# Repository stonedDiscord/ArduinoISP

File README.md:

# ArduinoISP

A PCB to use an Arduino Nano as an In-Circuit Serial Programmer (ISP) for programming AVR microcontrollers.

## Overview

This board makes it easier for an Arduino Nano to function as an ISP programmer, enabling you to burn bootloaders to other Arduinos and program AVR chips like the ATmega series, or ATtiny microcontrollers.
To do that, it connects the Arduino Nano correctly to the microcontroller's SPI pins (MOSI, MISO, SCK) and reset pin.
The board is designed in a way that the 6-pin socket header can be directly soldered to the board vertically, while the 10-pin header can accept a flat cable with an adapter on the other end, similiar to the many USBASP clones.

## Hardware

The PCB includes:

- **Two 15-pin headers** for connecting to an Arduino Nano:
  - **J1 (Analog)**: Pins for A0-A7, AREF, 3V3, and power
  - **J2 (Digital)**: Pins for D0-D13, GND, and power
- **AVR-ISP-10 connector (J3)**: Standard 10-pin ICSP programming header for target devices
- **AVR-ISP-6 connector (J4)**: Standard 6-pin ICSP programming header for target devices
- **3 Status LEDs**: Heartbeat, Error and Program
- **Pull-up resistors (R2, R3)**: 220Ω current limiting for LEDs

### Assembly
- Start with the SMD resistors
- Next solder the LEDs
- Then the 2 6-Pin connectors
- Next solder the 10-Pin connector
- Do the 2 Arduino headers last

### Pin Mapping

The ISP programming uses the following connections from the Nano to the 6-pin ICSP connector:

| ISP Pin | Signal | Nano Pin |
|---------|--------|----------|
| 1 | MISO | D12 |
| 2 | VCC | +5V |
| 3 | SCK | D13 |
| 4 | MOSI | D11 |
| 5 | RST | D10 |
| 6 | GND | GND |

The standard ICSP header pinout looks like this, with the key (if present) next to SCK
|   |   |
|---|---|
| MISO | VCC |
| ] SCK | MOSI |
| RST | GND |

## Usage

### 1. Program the Arduino Nano

1. Open the ArduinoISP sketch: `File > Examples > 11.ArduinoISP > ArduinoISP`
2. Select your Nano board and port
3. Upload the sketch to the Nano

You can also find the sketch on the [official Arduino GitHub page](https://github.com/arduino/arduino-examples/blob/main/examples/11.ArduinoISP/ArduinoISP/ArduinoISP.ino)

### 2. Wire the Boards

Connect the Nano to this PCB's headers. The board will provide the 6-pin ISP connector for connecting to your target device.

### 3. Burn the Bootloader

1. Select the target board type in `Tools > Board`
2. Select `Arduino as ISP` in `Tools > Programmer`
3. Use `Tools > Burn Bootloader`

## Requirements

- Arduino Nano
- Target AVR microcontroller board
- Arduino IDE

## Notes

- Be cautious when programming 3.3V devices (Due, Zero, etc.) - ensure the jumper is set correctly.

## Sponsor
This project is participating in the 2026 [Kicad PCB Design Contest](https://www.pcbway.com/activity/2026-kicad-pcb-design-contest.html).
[You can check out the project on the PCBway website](https://www.pcbway.com/project/shareproject/Arduino_Nano_ISP_Adapter_d65e29b3.html).

## Acknowledgements
- A similiar project for the Arduino Uno can be found at https://github.com/atoomnetmarc/Arduino-as-ISP-shield

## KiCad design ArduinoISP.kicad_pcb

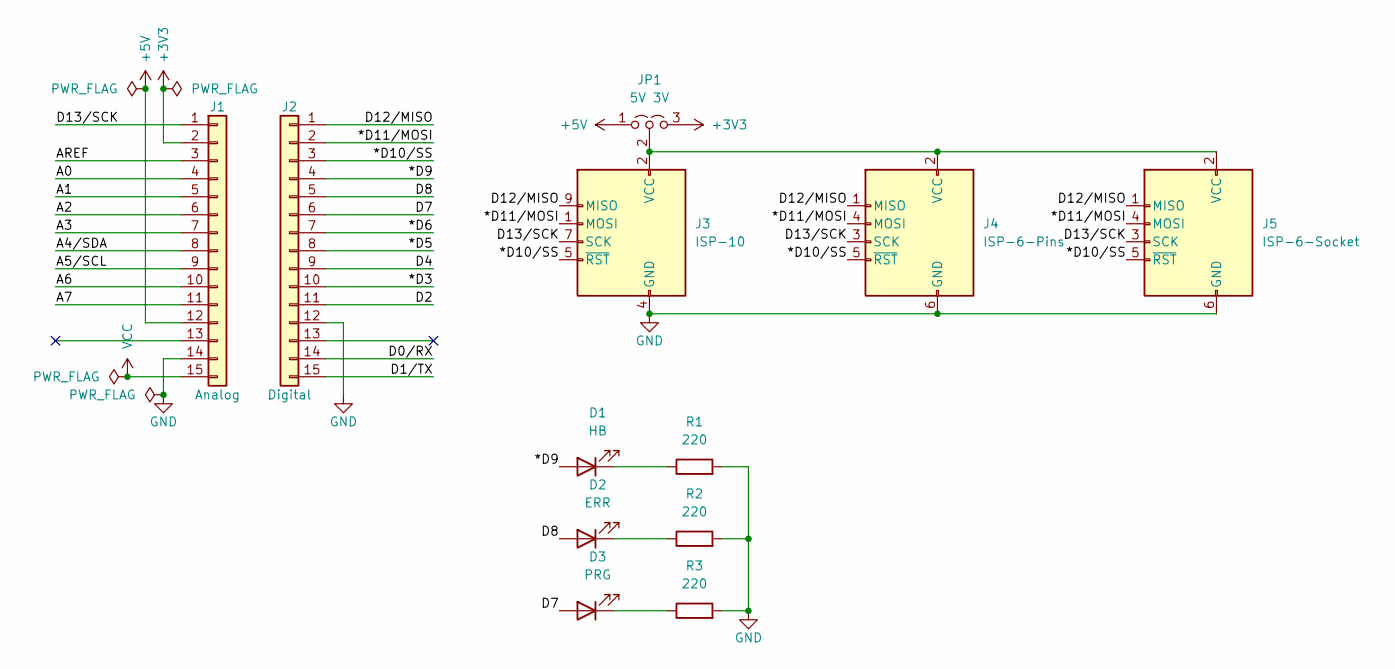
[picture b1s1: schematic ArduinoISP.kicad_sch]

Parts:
D1: HB; LED_0603_1608Metric_Pad1.05x0.95mm_HandSolder; MPN GL0603UG01
D2: ERR; LED_0603_1608Metric_Pad1.05x0.95mm_HandSolder; MPN GL0603UR01
D3: PRG; LED_0603_1608Metric_Pad1.05x0.95mm_HandSolder; MPN GL0603UY01
J1: Analog; PinSocket_1x15_P2.54mm_Vertical; MPN 2541FV-15P-B
J2: Digital; PinSocket_1x15_P2.54mm_Vertical; MPN 2541FV-15P-B
J3: ISP-10; IDC-Header_2x05_P2.54mm_Vertical; MPN DS1013-10SSiB1-B-0
J4: ISP-6-Pins; IDC-Header_2x03_P2.54mm_Horizontal; MPN DS1013-06SSiB1-B-0
J5: ISP-6-Socket; IDC-Header_2x03_P2.54mm_Horizontal; MPN DS1023-32-2x3V8
JP1: 5V 3V; PinHeader_1x03_P2.54mm_Vertical; MPN 2541WV-03P
R1, R2, R3: 220; R_0603_1608Metric_Pad0.98x0.95mm_HandSolder; MPN FRC0603F2200TS

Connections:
+3V3: J1.2, JP1.3 (B)
+5V: J1.12, JP1.1 (A)
/*D3: J2.10
/*D5: J2.8
/*D6: J2.7
/*D9: D1.2 (A), J2.4
/*D10/SS: J2.3, J3.5 (~RST), J4.5 (~RST), J5.5 (~RST)
/*D11/MOSI: J2.2, J3.1 (MOSI), J4.4 (MOSI), J5.4 (MOSI)
/A0: J1.4
/A1: J1.5
/A2: J1.6
/A3: J1.7
/A4/SDA: J1.8
/A5/SCL: J1.9
/A6: J1.10
/A7: J1.11
/AREF: J1.3
/D0/RX: J2.14
/D1/TX: J2.15
/D2: J2.11
/D4: J2.9
/D7: D3.2 (A), J2.6
/D8: D2.2 (A), J2.5
/D12/MISO: J2.1, J3.9 (MISO), J4.1 (MISO), J5.1 (MISO)
/D13/SCK: J1.1, J3.7 (SCK), J4.3 (SCK), J5.3 (SCK)
GND: J1.14, J2.12, J3.4 (GND), J3.6 (GND), J3.8 (GND), J3.10 (GND), J4.6 (GND), J5.6 (GND), R1.2, R2.2, R3.2
unnamed: D1.1 (K), R1.1
unnamed: D2.1 (K), R2.1
unnamed: D3.1 (K), R3.1
unnamed: J3.2 (VCC), J4.2 (VCC), J5.2 (VCC), JP1.2 (C)
VCC: J1.15

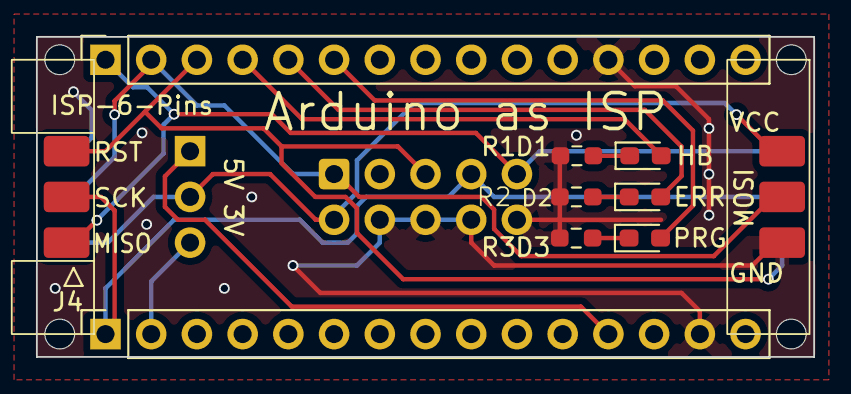
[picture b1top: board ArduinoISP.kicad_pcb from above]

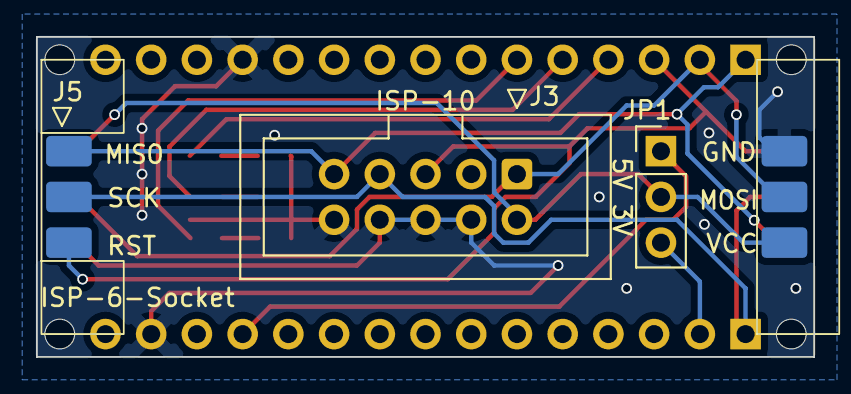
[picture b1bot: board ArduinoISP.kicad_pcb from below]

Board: 2 copper layers, 43.2 x 17.8 mm, 16 parts (3 on the bottom side), 14 nets.

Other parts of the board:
MH1, MH2, MH3, MH4: MountingHole_65mil

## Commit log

2026-05-11 move project files from automatenplatinen
2026-05-11 add footprints
2026-05-11 add image
2026-05-11 old image
2026-05-11 try double ended
2026-05-11 assembly
2026-05-11 new render
2026-05-11 clearance
2026-05-11 redo board
2026-05-11 part numbers
2026-05-11 renders
2026-05-11 uno link
2026-05-15 contest
